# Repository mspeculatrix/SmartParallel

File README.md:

# SmartParallel

A KiCad-based hardware project to create a 'smart' serial to parallel adapter, initially to allow printing to dot matrix printers. It is designed not just to turn a serial stream into eight-bit parallel but also deal with certain of the other lines used in Centronics interfaces, such as /Strobe etc.

Uses a TTL serial connection to a client machine (such as a Raspberry Pi). This connects to an Atmel ATMEGA328PB microcontroller.

The microcontroller sets up the eight data lines using a 74HC595 shift register. Other Centronics signals, such as /Strobe, are handled via a 74HC541 tri-state buffer.

There are verious LEDs providing blinkenlights - some with their logic inverted via a 74HC14 Schmitt inverter IC.

An ISP header allows programming of the microcontroller.

An I2C header is provided - this is intended for an LCD display (optional).

THIS IS A WORK IN PROGRESS and is far from complete.

See: https://mansfield-devine.com/speculatrix/category/projects/smartparallel/

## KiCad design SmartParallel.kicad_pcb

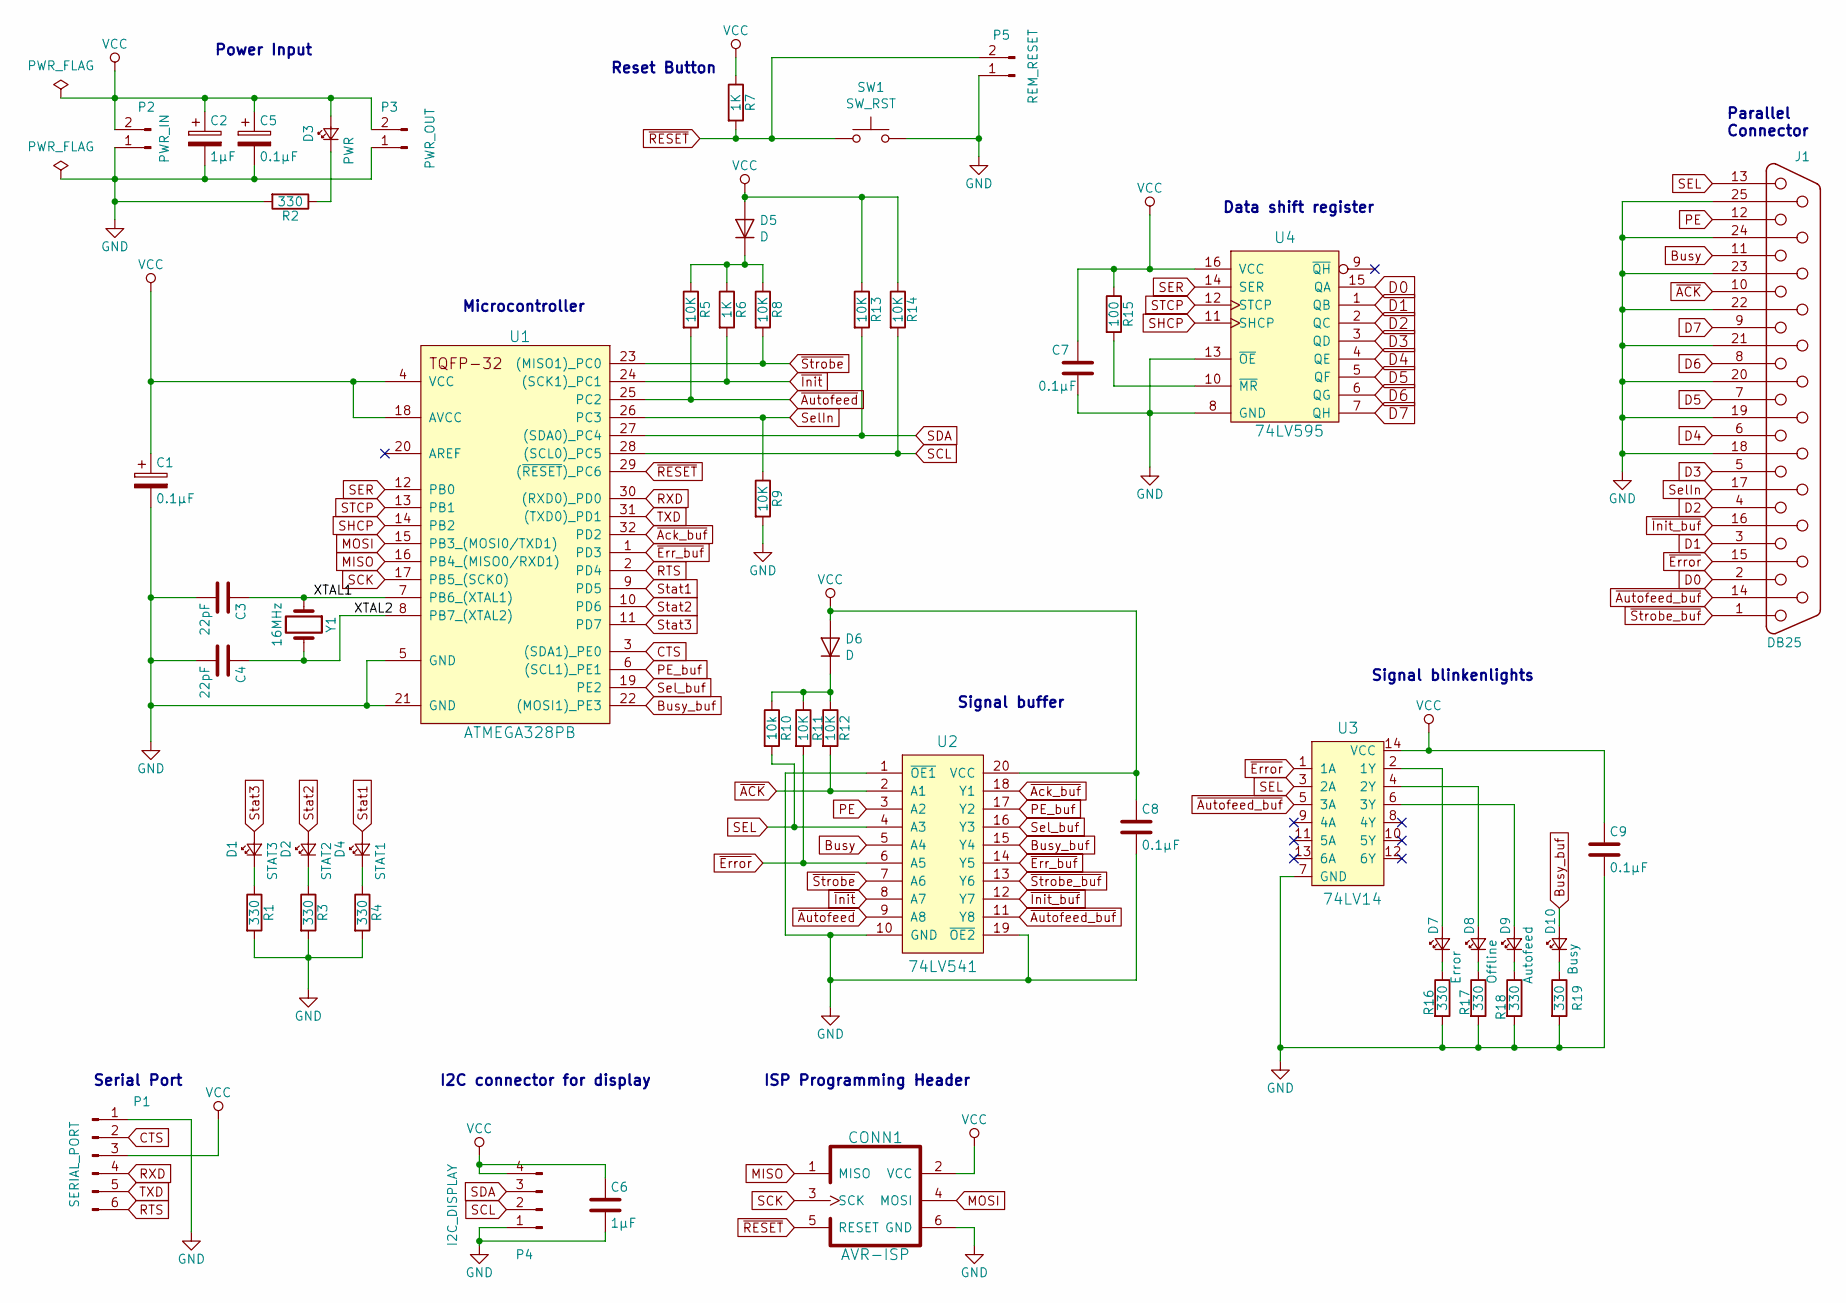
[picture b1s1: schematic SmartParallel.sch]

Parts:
C1, C5, C7, C8, C9: 0.1µF; C_1206
C2, C6: 1µF; C_1206
C3, C4: 22pF; C_1206
CONN1: AVR-ISP; AVR_ISP_HE10_2x3
D1: STAT3; LED_1206
D2: STAT2; LED_1206
D3: PWR; LED_1206
D4: STAT1; LED_1206
D5, D6: D; Diode_SOD-123F-S-FLAT
D7: Error; LED_1206
D8: Offline; LED_1206
D9: Autofeed; LED_1206
D10: Busy; LED_1206
J1: DB25; DB25FC
P1: SERIAL_PORT; Pin_Header_Angled_1x06
P2: PWR_IN; Pin_Header_Angled_1x02
P3: PWR_OUT; Pin_Header_Straight_1x02
P4: I2C_DISPLAY; Pin_Header_Straight_1x04
P5: REM_RESET; Pin_Header_Straight_1x02
R1, R2, R3, R4, R16, R17, R18, R19: 330; R_1206
R5, R8, R9, R11, R12, R13, R14: 10K; R_1206
R6, R7: 1K; R_1206
R10: 10k; R_1206
R15: 100; R_1206
SW1: SW_RST; SW_PUSH_6mm
U1: ATMEGA328PB; TQFP-32_7x7mm_Pitch0.8mm
U2: 74LV541; SOIC-20W_7.5x12.8mm_Pitch1.27mm
U3: 74LV14; SOIC-14_3.9x8.7mm_Pitch1.27mm
U4: 74LV595; SOIC-16_3.9x9.9mm_Pitch1.27mm
Y1: 16MHz; Crystal_SMD_EuroQuartz_MQ2-2pin_7.0x5.0mm

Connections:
/XTAL1: C3.1, U1.7 (PB6_(XTAL1)), Y1.1
/XTAL2: C4.1, U1.8 (PB7_(XTAL2)), Y1.2
Busy: J1.11, U2.5 (A4)
Busy_buf: D10.2 (A), U1.22 ((MOSI1)_PE3), U2.15 (Y4)
CTS: P1.2, U1.3 ((SDA1)_PE0)
D0: J1.2, U4.15 (QA)
D1: J1.3, U4.1 (QB)
D2: J1.4, U4.2 (QC)
D3: J1.5, U4.3 (QD)
D4: J1.6, U4.4 (QE)
D5: J1.7, U4.5 (QF)
D6: J1.8, U4.6 (QG)
D7: J1.9, U4.7 (QH)
GND: C1.2, C2.2, C3.2, C4.2, C5.2, C6.2, C7.2, C8.2, C9.2, CONN1.6 (GND), J1.18, J1.19, J1.20, J1.21, J1.22, J1.23, J1.24, J1.25, P1.1, P2.1, P3.1, P4.1, P5.1, R1.2, R2.2, R3.2, R4.2, R9.2, R16.2, R17.2, R18.2, R19.2, SW1.2, U1.5 (GND), U1.21 (GND), U2.1 (~OE1), U2.10 (GND), U2.19 (~OE2), U3.7 (GND), U4.8 (GND), U4.13 (~OE)
MISO: CONN1.1 (MISO), U1.16 (PB4_(MISO0/RXD1))
MOSI: CONN1.4 (MOSI), U1.15 (PB3_(MOSI0/TXD1))
unnamed: D1.1 (K), R1.1
unnamed: D2.1 (K), R3.1
unnamed: D3.1 (K), R2.1
unnamed: D4.1 (K), R4.1
unnamed: D5.1 (K), R5.1, R6.1, R8.1
unnamed: D6.1 (K), R10.1, R11.1, R12.1
unnamed: D7.1 (K), R16.1
unnamed: D7.2 (A), U3.2 (1Y)
unnamed: D8.1 (K), R17.1
unnamed: D8.2 (A), U3.4 (2Y)
unnamed: D9.1 (K), R18.1
unnamed: D9.2 (A), U3.6 (3Y)
unnamed: D10.1 (K), R19.1
unnamed: R15.2, U4.10 (~MR)
PE: J1.12, U2.3 (A2)
PE_buf: U1.6 ((SCL1)_PE1), U2.17 (Y2)
RTS: P1.6, U1.2 (PD4)
RXD: P1.4, U1.30 ((RXD0)_PD0)
SCK: CONN1.3 (SCK), U1.17 (PB5_(SCK0))
SCL: P4.2, R14.2, U1.28 ((SCL0)_PC5)
SDA: P4.3, R13.2, U1.27 ((SDA0)_PC4)
SEL: J1.13, R10.2, U2.4 (A3), U3.3 (2A)
SER: U1.12 (PB0), U4.14 (SER)
SHCP: U1.14 (PB2), U4.11 (SHCP)
STCP: U1.13 (PB1), U4.12 (STCP)
SelIn: J1.17, R9.1, U1.26 (PC3)
Sel_buf: U1.19 (PE2), U2.16 (Y3)
Stat1: D4.2 (A), U1.9 (PD5)
Stat2: D2.2 (A), U1.10 (PD6)
Stat3: D1.2 (A), U1.11 (PD7)
TXD: P1.5, U1.31 ((TXD0)_PD1)
VCC: C1.1, C2.1, C5.1, C6.1, C7.1, C8.1, C9.1, CONN1.2 (VCC), D3.2 (A), D5.2 (A), D6.2 (A), P1.3, P2.2, P3.2, P4.4, R7.1, R13.1, R14.1, R15.1, U1.4 (VCC), U1.18 (AVCC), U2.20 (VCC), U3.14 (VCC), U4.16 (VCC)
~ACK: J1.10, R12.2, U2.2 (A1)
~Ack_buf: U1.32 (PD2), U2.18 (Y1)
~Autofeed: R5.2, U1.25 (PC2), U2.9 (A8)
~Autofeed_buf: J1.14, U2.11 (Y8), U3.5 (3A)
~Err_buf: U1.1 (PD3), U2.14 (Y5)
~Error: J1.15, R11.2, U2.6 (A5), U3.1 (1A)
~Init: R6.2, U1.24 ((SCK1)_PC1), U2.8 (A7)
~Init_buf: J1.16, U2.12 (Y7)
~RESET: CONN1.5 (RESET), P5.2, R7.2, SW1.1, U1.29 ((~RESET~)_PC6)
~Strobe: R8.2, U1.23 ((MISO1)_PC0), U2.7 (A6)
~Strobe_buf: J1.1, U2.13 (Y6)

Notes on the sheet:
ISP Programming Header
I2C connector for display
Serial Port
Power Input
Reset Button
Data shift register
Signal buffer
Signal blinkenlights
Microcontroller
Parallel Connector

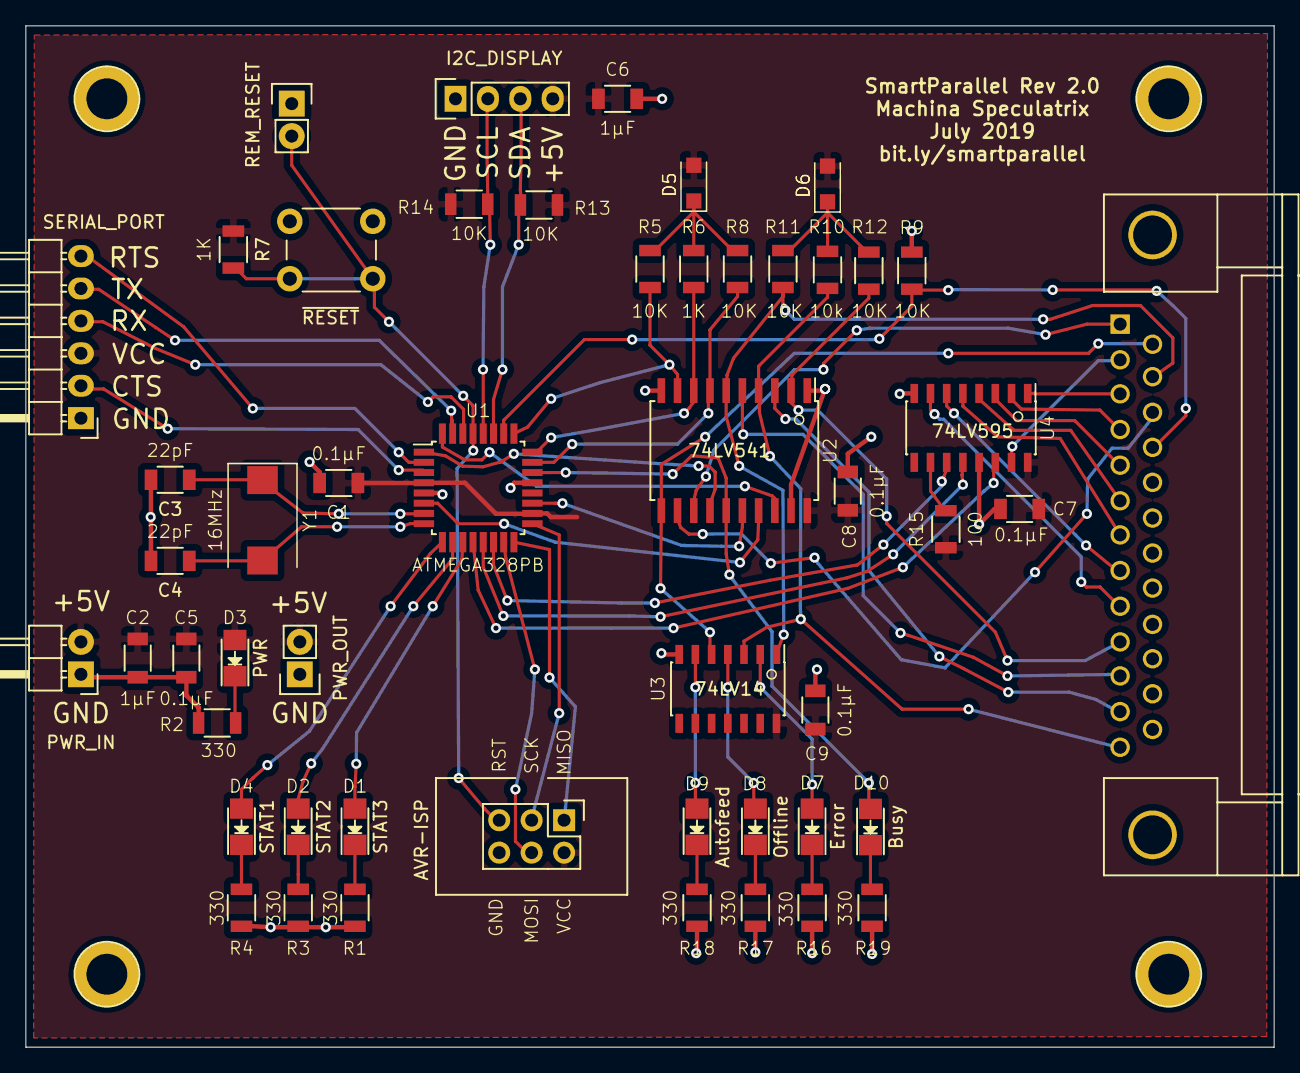
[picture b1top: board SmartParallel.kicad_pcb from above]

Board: 2 copper layers, 97.8 x 80.0 mm, 51 parts (0 on the bottom side), 59 nets.

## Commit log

2019-05-24 First upload
2019-05-24 Fixed library issues
2019-05-24 Fixed library issue
2019-05-24 Minor updates
2019-06-06 First completed PCB
2019-06-06 minor update
2019-07-05 many small changes
2019-07-12 Final version of Rev.2.0 schematic
2019-07-23 Misc tweaks
